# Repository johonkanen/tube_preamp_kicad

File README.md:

# tube_preamp_kicad

KiCad 10 migration of the 3-tube 12AX7 preamp (`etunen`) of the tube amplifier, from Proteus. The schematic is redrawn from
the Proteus PDF and the PCB is rebuilt from the Gerber X2 export, so that every pad, track,
via and pour carries a net from the new schematic. The IPC-D-356A netlist of the CADCAM export
is the reference that every check compares against.

This is **rev A, the as-built baseline**. The redesign (ribbon cables, PCB-mount pots, the new
power section) starts from it. The amplifier project, its specification and the hardware state
are in [tube_amplifier_kicad](https://github.com/johonkanen/tube_amplifier_kicad), which includes
this repo as a submodule once the conversion is verified.

## Method

The shared [proteus2kicad](https://github.com/johonkanen/proteus2kicad) tools, a submodule in
`tools/p2k` (clone with `git clone --recurse-submodules`, or run `git submodule update --init`).
The phases and checks are in `tools/p2k/CONVERSION_PLAYBOOK.md`. Everything specific to this
board is in `p2k_config.py`.

## Status

Conversion plan: [PLAN.md](PLAN.md); progress: [STATUS.md](STATUS.md); prompt for the next agent session: [next_prompt.md](next_prompt.md).

Phase 0 (skeleton and inventory) done 2026-11-20: `p2k_config.py` complete, `reference/`
tables from the IPC netlist. Phase 1 (schematic) done 2026-11-20: `lib/part_map.csv` (163 parts),
`lib/tube_preamp.kicad_sym` (9 symbols, pins = IPC ids), 5 sheets drawn by `tools/sheets/sheet01-05.py`:
163/163 parts, the KiCad netlist equals the Proteus IPC netlist (98 nets, 0 wrong-net pins), ERC
0 errors / 0 warnings. Phase 2 (footprints) done 2026-11-20: `tools/gen_footprints.py` →
`lib/footprint_map.csv` and `lib/tube_preamp.pretty`, all 163 parts fit the IPC pads (worst residual
0.001 mm), pin order checked (`tools/check_pin_order.py`). User decisions 2026-11-20: the noval
sockets are on the solder side (bottom footprint in Phase 5), the KiCad drills are kept (`DRILL_SMALLER`).
Phase 3 (PCB) done 2026-11-20: `tools/make_pcb.sh` builds `kicad/tube_preamp.kicad_pcb`
reproducibly (747 tracks, 14 vias, 13 mounting holes H101-H113), copper 0 shorts / 0 orphans / 0
opens, `check_board` OK, DRC 0 shorts / 0 unconnected / 0 parity / no unaccepted errors (user
decision 2026-11-20: round 1.5 mm TO-92 pad 1 on Q1-Q9). Still open for the user: the values of R13,
R22, R27, R30, R34, R51 and Q4. Phase 4 (independent verification, a fresh session) done 2026-11-20: `p2k ipc356_diff` (KiCad's own
IPC-D-356 export vs the Proteus file: 366/366 records within 0.05 mm, 98 nets 1:1) and the gerber
round trip `tools/roundtrip.py` (copper XOR per layer: only pad-shape differences; drills 366/366;
the 2010 Excellon 364/364 plus the 2 vias added in October 2010) pass and are in `tools/check_all.sh`;
the PDF was re-read against the IPC on all five sheets without a disagreement.
Phase 5 (clean-up) done 2026-11-20: the noval sockets U1-U3 are on the bottom side with the standard
noval numbering (footprint built mirrored; copper, pads and nets unchanged), references placed by
`place_refdes`, the short Proteus track pieces kept as drawn (user decisions), and two hardened checks
from the PI / FX loop board (`tools/check_drill_smaller.py`, joined no-connect pins in `tools/compare.py`
/ `tools/erc.sh`). `tools/check_all.sh`: ALL CHECKS PASSED. **The conversion is complete.** The board
is still generated by `tools/make_pcb.sh` (STATUS.md "Phase 5").
Design fixes 2026-11-20 (user decisions, STATUS.md "Design fixes 2026-11-20"): the G5V-2 relay symbol
carries Omron's terminal names (finding 14; pin numbers = Proteus ids, no copper change), the 9
dangling / zero-length Proteus track pieces of findings 16 / 20 are not built (`REMOVED_TRACKS`, pinned by
`tools/check_removed_tracks.py`; 738 tracks), the component values stay as they are (the board will be
redesigned) and finding 4 is unchanged. `tools/check_all.sh`: ALL CHECKS PASSED. Next: the shared-tool
migration, then the board stops being generated (next_prompt.md).
Shared-tool migration 2026-11-20 (STATUS.md "Shared-tool migration 2026-11-20"), done: p2k a9a286c;
the board-local tools named above (`compare.py`, `erc.sh`, `check_pin_order.py`, `rename_holes.py`,
`roundtrip.py`, `check_drill_smaller.py`, `excellon_metric.py`, `measure_gaps.py`) are replaced by the
shared tools and `p2k_config.py` keys (`tools/make_pcb.sh` = `p2k make_pcb`); no strict-check opt-outs;
kept: `tools/check_removed_tracks.py`. Design change (electrically identical, same copper): the relays
RLY1-RLY5 carry the Omron pin numbers (`IPC_PIN_IDS`) with KiCad's stock G5V-2 symbol and footprint.
Generation stopped 2026-11-20 (user decision, STATUS.md "Generation stopped 2026-11-20"): the
committed KiCad files are the source from now on; the generators named above are frozen in `tools/generate/`.

Built in about 2010 from the June 2010 Gerbers (`source/fab_2010/`). The Proteus layout was edited in October 2010: Q6 pin 3 moves from net J1 to a new net J4 (Q6-3, Q9-3, pad D), plus a ground reroute. The export in `source/cadcam/` is the October version. Holes, outline and tube sockets are identical to the fabricated board. Accepted as the baseline, since the board gets redesigned.

## Working on rev A (since 2026-11-20)

Rev A is no longer generated from the Proteus data. The committed KiCad files are the source:
open `kicad/tube_preamp.kicad_pro` in KiCad 10 and edit the schematic, the board and `lib/`
there. Then run `tools/check_all.sh` (must end with ALL CHECKS PASSED). It checks the
committed files against the Proteus truth (IPC netlist, gerbers, drills) and KiCad's rules:
netlist, ERC, footprints, pin order, board pads / vias / holes, copper connectivity, DRC with
parity, KiCad's IPC-D-356 export and the gerber round trip. A change that makes the board
differ from Proteus fails a check on purpose: record it as a deviation (the matching
`p2k_config.py` key with a reason and a line in STATUS.md), never hide it.

The generator scripts in `tools/generate/` are frozen history (how every file was made) and
must not be run; `tools/generate/make_pcb.sh` refuses without `--force-regenerate`.

**Rev B** (the redesign, preamp design D) is a separate KiCad project in [`rev_b/`](rev_b/),
worked on in its own sessions; `tools/check_all.sh` checks only rev A.

## Source

etunen.DSN/.LYT (Proteus 7, 2010), opened and saved in Proteus 8.12 as `etunen.pdsprj`. Exported 2026-11-19 from Proteus 8.12 SP2: schematic PDF, Gerber X2 CADCAM (metric)
with the IPC-D-356A netlist.

## Mechanical baseline

From the export (the fit reference for the redesign; the KiCad file is
`mechanical/preamp_etunen.kicad_pcb` in tube_amplifier_kicad):

```
outline: 382.79 x 71.91 mm, lower-left corner at (-195.357, -45.730) in the Proteus frame
copper layers: 2; components: 163; mounting holes: 13
mounting holes (relative to the lower-left outline corner, mm; KiCad refdes H101-H113,
mapping in STATUS.md "Phase 3"):
  H1: x   55.992  y   58.550  drill 3.00 plated
  H2: x  163.492  y   61.550  drill 3.00 plated
  H3: x  194.492  y   58.550  drill 3.00 plated
  H4: x  174.492  y   36.050  drill 3.00 plated
  H5: x   34.992  y   36.050  drill 3.00 plated
  H6: x    5.492  y    5.050  drill 3.00 plated
  H7: x    5.492  y   66.050  drill 3.00 plated
  H8: x  247.492  y   61.550  drill 3.00 plated
  H9: x  277.492  y   58.550  drill 3.00 plated
  H10: x  258.492  y   36.050  drill 3.00 plated
  H11: x  378.492  y    5.050  drill 3.00 plated
  H12: x  378.492  y   66.050  drill 3.00 plated
  H13: x   24.492  y   61.550  drill 3.00 plated
```

## Layout

```
source/         Proteus exports (read-only)
  cadcam/         Gerber X2 export with the IPC-D-356A netlist (the reference)
  schematic_pdf/  schematic PDF to redraw from
  *.pdsprj        Proteus project (schematic values, devices, packages, pin names)
  fab_2010/       the RS-274X Gerbers the boards were made from (June 2010)
reference/      tables derived from the IPC netlist (p2k ipc356): pads, pin -> net, pins by net
tools/p2k/       proteus2kicad (submodule)
kicad/, lib/     rev A KiCad project and libraries (the source since 2026-11-20)
tools/check_all.sh  every verification step (run at the start and end of a session)
tools/check_removed_tracks.py  board check: the decided removed Proteus track pieces
tools/generate/  frozen generators (history, do not run)
rev_b/          rev B, the redesign (separate project)
p2k_config.py   board configuration for the tools
```

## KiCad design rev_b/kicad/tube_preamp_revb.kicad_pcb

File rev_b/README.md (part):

# Preamp rev B (design D): first-draft schematic

The next preamp board, from the simulations in
[tube_amplifier_kicad](https://github.com/johonkanen/tube_amplifier_kicad) (branch `tube_preamps`):
`sim/preamp_voicing` (design D, `ours/chain_d.py` + `ours/fit_design_D.json`) and
`docs/preamp_board_plan.md`. Rev A (the as-built `etunen` conversion) at the repo root is not
touched; `rev_b/` is its own p2k board root (`p2k_config.py`, PROJECT `tube_preamp_revb`).

Three channels (clean / crunch / lead) on one shared 3x12AX7 cascade: S1, S2, (S5), S3, a
self-biased CF, three Baxandalls, S4 recovery, attenuator, output mute. Switching follows CH-5
(DC-neutral): 7 MMBFJ113 shunts (6 pot-set selections + output mute), 5 2N7002 low-side AC
cathode networks, 4 G6K-2 relays (S2 treble bleed, S5 routing, c2, S3 treble bleed), 16 control
lines from an MCP23S17.

## Build

```
python3 rev_b/tools/make_lib.py          # lib/tube_preamp_revb.kicad_sym from KiCad's stock libraries (flattened)
python3 rev_b/tools/make_project.py      # project, root sheet, empty sub-sheets
python3 -I rev_b/tools/make_footprints.py  # project footprints, lib/footprint_map.csv (from make_bom.py), fp-lib-table
python3 rev_b/tools/sheets/draw_all.py   # draws all five sheets (overwrites them); Footprint fields from the map
python3 -I rev_b/tools/make_footprints.py --check   # every part has a footprint, symbol pins = pads
tools/p2k/bin/kipy rev_b/tools/make_pcb.py   # NEW board from the netlist (refuses once it has tracks)
```

`make_pcb.py` is for the start only: once placement begins, the board is edited in KiCad and
schematic changes go in with Update PCB from Schematic (the footprints carry the schematic links).

The sheets are generated: edit `tools/sheets/draw_all.py`, not the `.kicad_sch` files, until the
draft is frozen. Drawing style is netlist-first (parts on a grid, a wire stub and a label on every
pin), exact for ERC and the netlist; a tidy layout pass comes later. ERC: 0 errors, 0 warnings
(KiCad 10, `kicad-cli sch erc`).

| Sheet | Contents |
|---|---|
| 01 | Input jack, 68k, S1 (V1 pins 1-3) with its DC 2.7k and two MOSFET AC networks; per-channel coupling cap, gain pot (ribbon), bright cap, JFET T-selection into S2 |
| 02 | S2 (V1 6-8), S5 (V2 1-3), S3 (V2 6-8); relays K201-K204; the AC networks |
| 03 | CF (V3 1-3, grid at 90 V), three Baxandalls (pots on the ribbons), JFET-selected post-gain into S4 (V3 6-8), 330k / 220k attenuator, output mute JFET |
| 04 | Control ribbon, MCP23S17, 2x DG412 (JFET gates 0 / -15 V), 74LVC1G08 (unmute = GPA6 AND MUTE_ALL_N), ULN2003 (relay coils) |
| 05 | B+ regulator (as `sim/preamp_supply/reg.py`), RC decoupling per stage, 90 V CF bias, heaters + reference jumper, three 26-pin pot ribbons, output |

## Draft decisions and open items

- Values follow the 2026-11-20 refit of design D (gain-knob penalty): the lead's 470k pad and 1 nF
  bright cap are gone. The refit also gave S2 a lead-only 4.7k + 22 µF network; it is drawn
  **permanent** (no switch), in parallel with the clean / crunch switched 22 µF, which keeps the
  control lines at 16. Simulated: identical fit (crunch cost 10.03 → 10.04, others unchanged).
- Fail-safe muting: DG412 is normally open, so with no logic supply, reset, or no -15 V every JFET
  gate sits at 0 V (JFET on) and the output is muted; a missing control ribbon pulls MUTE_ALL_N low.
- 2N7002 gates run from the expander's 5 V (the plan said 10 V); Rds(on) at 5 V is a few ohms
  against 1.5k-10k cathode resistors. Check the 22 µF / 1M bleed timing with the real Vgs(th).
- Relays: Omron G6K-2F-Y 5 VDC, decided 2026-11-22 (main session; same part on the PI + FX board).
  Checked against the Omron G6K datasheet (top view): coil + pin 1, - pin 8; pole 1 COM 3, NC 4,
  NO 2; pole 2 COM 6, NC 5, NO 7. Every switched function is on the NO contacts, so energized =
  the lead / crunch setting and an unpowered board sits in the clean wiring (the first draft had
  2 / 4 and 5 / 7 the other way round; fixed 2026-11-22). Coil 21.1 mA at 5 V (237 Ω), 4 coils.
  Contacts carry no DC (10M bleeds, CH-5 rule 3); K201 / K204 sit at the B+ DC level, within the
  coil-to-contact insulation of the -Y (3.2 mm) version.
- Open from the fit: the crunch's gain knob stays at 0.9 and its JFET node at 9.3 V peak with 1 V
  in (limit 8 V); a pad on the crunch's input network is the next fix. The footprint is in: R119
  (0805) between C108 and the crunch gain pot's top, fitted as a 0R link until the voicing sim
  sets the value (2026-11-22).
- B+ decoupling resistors (3.3k / 6.8k / 10k / 10k) are provisional until the stage currents are
  summed; the simulations used 300 V at the plates' supply. All four are 2512 (2026-11-22), so a
  later value change doesn't touch the layout.
- HV resistors split for 200 V 2512 parts (2026-11-21): the B+ bleed is R508 + R518 (2 x 220k, 165 V
  each) and the VB90 divider top R513 + R519 (2 x 330k, 115 V each; 660k with R514 270k gives
  VB90 = 0.29 x BP4, about +2 % on the old 680k). The regulator's foldback resistor is R507 + R520 +
  R521 (3 x 270k = 810k, was one 820k 1206): it sees the whole 430 V raw rail at start-up or into a
  short, 145 V per part. The reference filter Rf is R502 + R525 + R526 (3 x 330k = 990k, was one
  1M 1206; 2026-11-22, found by the PI + FX session): the 390 V zener reference sits across it while
  C501 charges, 130 V per part. Checked the rest of the board from the netlist: no other resistor
  sees more than 200 V in normal operation. The 10M cap bleeds (relay networks) see under 100 V at
  start-up and short recovery, and only a ~300 V pulse (22-220 ms) if B+ is hard-shorted; kept as 1206 (main session
  2026-11-22: the 200 V rule covers normal operation and start-up, a decaying fault pulse within the
  part's short-time overload rating is acceptable).
- Regulator short-circuit protection by thermal foldback (user 2026-11-21): Q502 is an STD4N80K5 DPAK
  on a copper pour, and Q503 (the current-limit NPN) sits on the same pour, thermally coupled but
  not electrically connected. Q503's Vbe falls about 2 mV/K, so a short heats the pour and folds the
  current back further; R507 stays about 820k (now 3 x 270k), R504 goes 20R -> 13R to keep the normal limit above the
  10-15 mA load when Q503 is warm. Simulated (sim/preamp_supply model, whole circuit at one
  temperature, 330 V output):

  | Q503 temperature | 0 C | 27 C | 50 C | 70 C | 85 C | 100 C |
  |---|---|---|---|---|---|---|
  | Normal limit (mA) | 38 | 33 | 28.5 | 25 | 22 | 19 |
  | Into a short (mA / W in Q502) | 16.5 / 7.1 | 12.3 / 5.3 | 8.6 / 3.7 | 5.4 / 2.3 | 3.0 / 1.3 | 0.5 / 0.2 |

  Start-up and recovery after a short work at every temperature. With about 30 K/W from the pour
  to Q503 the short settles near 80 C and 2 W. Lowering R507 instead was rejected: 700k gives 4 mA
  at 27 C but no start-up above about 70 C. Bench check: short B+ and watch the current settle.
- Drain resistor R522 + R523 + R524 (3 x 1.5k 2512 = 4.5k, raw rail to Q502's drain, placed off
  Q502's pour), user 2026-11-22 with the 70 C design temperature under the plate: it takes about
  68 V of the drop, so Q502 dissipates 0.5 W instead of 1.5 W and Q503 stays near 87-91 C at 70 C
  ambient (limit about 22 mA, 19 mA at 420 V raw; start-up works). Without it the regulator lost
  start-up above 60 C ambient. Short unchanged. See tube_amplifier_kicad docs/preamp_regulator.md
  and sim/preamp_supply/results/thermal_foldback.md. Raw rail at 480 V (HV supplies' trip level,
  2026-11-22): every raw-rail part is within its rating (LND150 sees about 90 V, R3 160 V per part);
  the regulator keeps running, but held at 480 V with Q503 at 85 C or more it doesn't start or
  recover from a short. Fine as a transient, sustained raw at most 450 V (preamp_regulator.md).
- Footprints (2026-11-22): every part has one, chosen on its line in `tools/make_bom.py` (the BOM
  and the footprints come from the same list; [bom/](bom/README.md), JLC search and stock check from
  the jlc-tools submodule rev_b/tools/jlc). KiCad stock footprints except three Faston tab
  footprints and the rev A noval socket (rev_b/lib/tube_preamp_revb.pretty). The generic transistor
  symbols got package pin numbers (make_lib.py: Q501 / Q502 1 G, 2 D, 3 S; Q503 1 B, 2 E, 3 C).
  Values set at the same time: R327 300k (for the PI + FX's 1 MΩ input), C105 / C108 / C111
  marked 630 V.
- Grounding (tube_amplifier_kicad docs/grounding.md §5a, confirmed by the user 2026-11-21): AGND
  (GNDA) is the signal and power star, its only entry J501 pin 2; the switch references (JFET and
  MOSFET sources, their gate caps, the JFET-gate pull-downs R419-R425) are AGND. Sheet 04's logic,
  expander pull-downs, ULN2003, relay coils and DG412 GND / rail decoupling are a DGND (GNDD) island
  joined to AGND only by R426 10 Ω ∥ C407 100 nF next to J401. Chassis bond: the CHASSIS pad J102
  next to J101: insulated input jack plus a bolted chassis tag wired to J102 (user, 2026-11-21;
  interfaces.md IF-1). J507 pin 3 is the shield, soft-tied here (R517 10 Ω ∥ C509 100 nF), solid at the
  PI + FX end. Heater reference stays on J503.
- Layout constraint (tube_amplifier_kicad docs/interfaces.md §12.2, components down confirmed by the
  user 2026-11-21; replaces the earlier "headers pass under the front edge" rule): the board hangs
  15 mm below the plate with its components down and the novals on the solder side. Along the front
  edge, at least at the three pot-ribbon positions, keep a strip 15 mm deep where no part is taller
  than 5 mm (SMD passives and SOT-23 only: no film or electrolytic caps, relays or headers). J504-J506
  are vertical shrouded headers on the downward face, set back about 20 mm from the front edge, and
  nothing (mated socket included) protrudes past the edge. Final check: the 3D fit with the front
  panel board once this board is laid out. Standoffs 15 mm; the `etunen` outline stays.
- Pot direction: on every pot ribbon line the CW (clockwise-end) lug takes the TOP net. Bass and
  treble: TOP is the boost end (C1 / C3 from the CF), BOT the cut end (22k to GND), so clockwise =
  more; gain and post: TOP is the signal, the bottom GND (confirmed to the front panel session
  2026-11-21). Pots (front panel board, decided 2026-11-22): Alpha 16 mm PCB pots (RV16AF-41
  class, M7 bushing); gain and post-gain 1M log, treble and bass 1M linear.
- Start-up (2026-11-22): the amp plays before Linux boots; the control board's FPGA brings it up on
  its own, so this board sees RESET_N, the SPI write, then unmute a few seconds after power-on.
- J401 placement: the control board (126 x 92 mm at chassis x 426-552, y 30-122) has its preamp
  ribbon connector on its front edge at about x 438-464, roughly 50-80 mm from J401 at this
  board's right end (main session 2026-11-22).
- Output (J507), agreed in tube_amplifier_kicad docs/interfaces.md §10 (2026-11-20): Zout about
  140k; the PI + FX input is ≥ 1 MΩ with a buffer at its connector, total capacitance on OUT
  ≤ 50 pF. The 1 MΩ load costs about 1.1 dB: the attenuator's 330k is now 300k (R327, 2026-11-22). Fallback if the cable can't be short: the divider moves to the receiver, which needs
  a re-run of sim/preamp_voicing/switching_real.py (mute depth). The connector pinouts are the
  interfaces.md contract: propose changes through the main-branch session.

## Layout (decisions 2026-11-22, user: "make decisions that allow completing the layout")

`kicad/tube_preamp_revb.kicad_pcb` is started (`tools/make_pcb.py`): outline, holes, sockets, the
interface connectors placed, net classes and clearance rules set, every other part parked below
the board by sheet. DRC with schematic parity: only the unrouted connections. Choices made so the
layout can be finished; to check against the other boards when they are laid out.

- **Frame:** the `etunen` outline (382.79 x 71.91 mm) in rev A's coordinates: chassis x = board
  x + 198.73, chassis y = board y + 42.35. The top edge (y -26.175) is the front, the left end is
  the input end. KiCad's front (F) side is the component side, facing down.
- **Board:** 2 layers, 1.6 mm, 2 oz copper (the regulator's 40 K/W pour estimate assumed 2 oz; set it in
  Board Setup > Physical Stackup before the fab outputs, the generated board has the default 1 oz).
  Min track / space 0.2 mm.
- **Sockets:** V1-V3 on the solder side (B), at rev A's U1-U3 positions and orientation (pads
  checked: 0.00 mm). The rev A footprint got a round courtyard and silk outline (the rectangle
  clipped the standoff holes H103-H105).
- **Mounting holes:** H101-H113 at the rev A positions, 3.2 mm, not plated, with an 8 mm copper
  keep-out. The chassis bond is J102 only (grounding.md §5a), so no hole is plated.
- **Pot ribbons:** J504 (clean) and J505 (crunch) between V1 and V2, J506 (lead) between V2 and
  V3, long axis along the front edge, body front edge 20 mm behind the board edge, odd (GND) pins
  on the rear row. Centres at board x -112 / -62 / 25 = **chassis x 86.7 / 136.7 / 223.7**, body
  front edge at chassis y 36.2. Three 41 mm headers don't fit in one gap between sockets; the
  lead's gain-pot lines then run about 120 mm to V1, inside the ground pour. Each channel's
  Baxandall and post-gain JFET go next to its header.
- **Other connectors:** J101 input and J102 chassis tab at the left end (chassis x about 9);
  J401 at the right end, clear of H102 (chassis x 375-385, y 27-54, about 60 mm from the control
  board's connector); J501 B+ raw tabs at the rear right (chassis x 357 / 372); J502 heater tabs
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
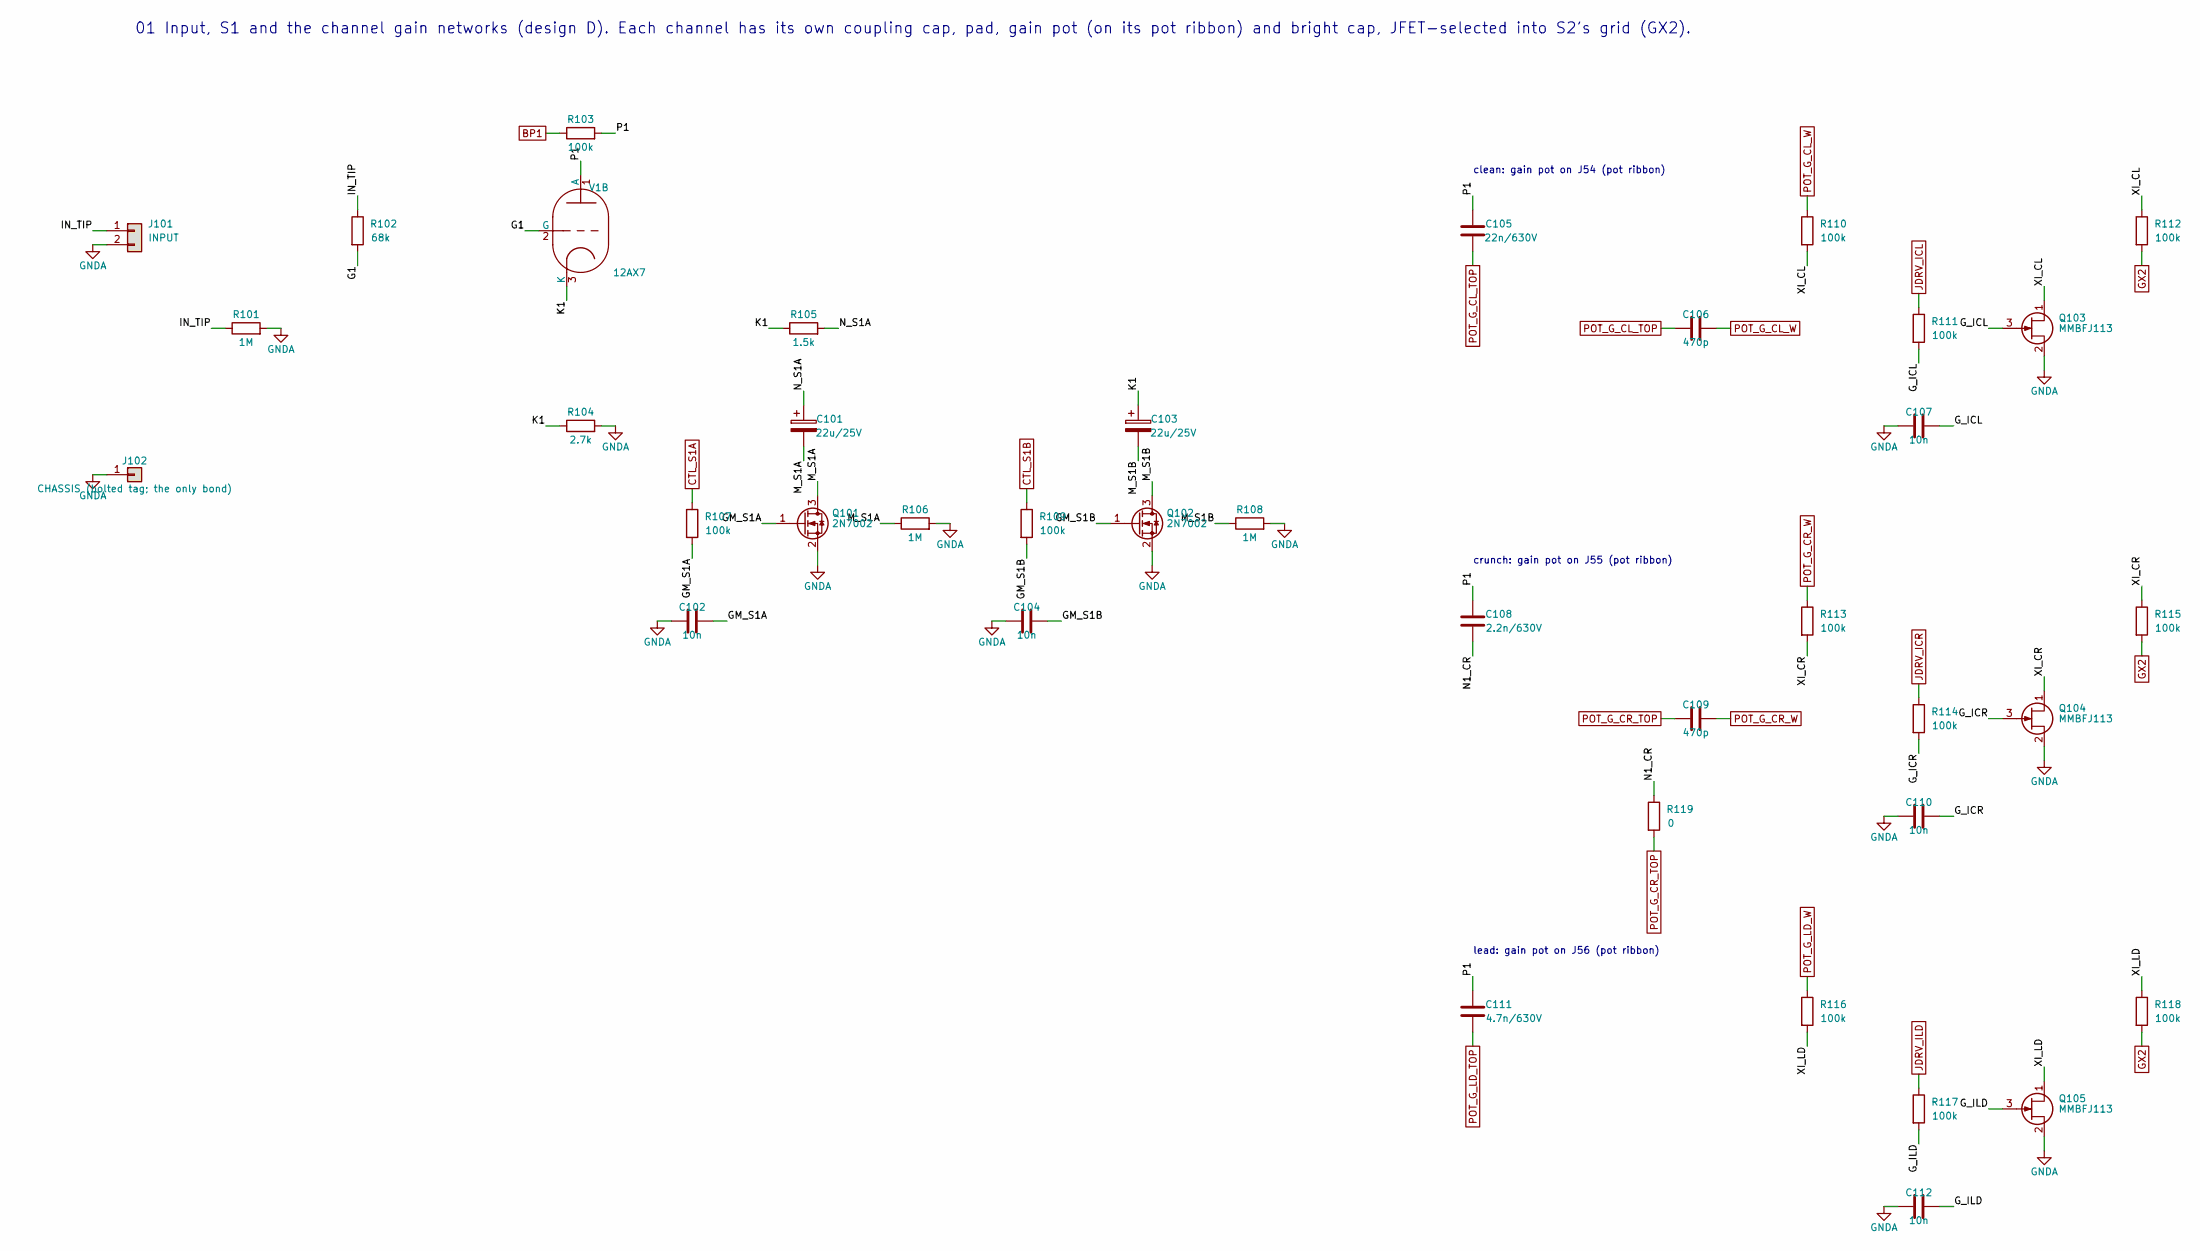
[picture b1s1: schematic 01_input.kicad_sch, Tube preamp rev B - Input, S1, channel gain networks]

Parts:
C101, C103: 22u/25V; CP_Elec_5x5.4
C102, C104, C107, C110, C112: 10n; C_0603_1608Metric
C105: 22n/630V; C_Rect_L10.0mm_W4.0mm_P7.50mm_MKS4
C106, C109: 470p; C_0805_2012Metric
C108: 2.2n/630V; C_1206_3216Metric
C111: 4.7n/630V; C_1206_3216Metric
J101: INPUT; Molex_KK-254_AE-6410-02A_1x02_P2.54mm_Vertical
J102: CHASSIS (bolted tag; the only bond); Faston_Tab_6.3mm_x1
Q101, Q102: 2N7002; SOT-23
Q103, Q104, Q105: MMBFJ113; SOT-23
R101, R106, R108: 1M; R_0805_2012Metric
R102: 68k; R_0805_2012Metric
R103: 100k; R_2512_6332Metric
R104: 2.7k; R_0805_2012Metric
R105: 1.5k; R_0805_2012Metric
R107, R109, R111, R114, R117: 100k; R_0603_1608Metric
R110, R112, R113, R115, R116, R118: 100k; R_0805_2012Metric
R119: 0; R_0805_2012Metric
V1: 12AX7; Valve_Noval_Belton_PCD21.00mm

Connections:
/01 Input, S1, channel gain networks/G1: R102.2, V1.2 (G)
/01 Input, S1, channel gain networks/GM_S1A: C102.1, Q101.1 (G), R107.2
/01 Input, S1, channel gain networks/GM_S1B: C104.1, Q102.1 (G), R109.2
/01 Input, S1, channel gain networks/G_ICL: C107.1, Q103.3 (G), R111.2
/01 Input, S1, channel gain networks/G_ICR: C110.1, Q104.3 (G), R114.2
/01 Input, S1, channel gain networks/G_ILD: C112.1, Q105.3 (G), R117.2
/01 Input, S1, channel gain networks/IN_TIP: J101.1, R101.1, R102.1
/01 Input, S1, channel gain networks/K1: C103.1, R104.1, R105.1, V1.3 (K)
/01 Input, S1, channel gain networks/M_S1A: C101.2, Q101.3 (D), R106.1
/01 Input, S1, channel gain networks/M_S1B: C103.2, Q102.3 (D), R108.1
/01 Input, S1, channel gain networks/N1_CR: C108.2, R119.1
/01 Input, S1, channel gain networks/N_S1A: C101.1, R105.2
/01 Input, S1, channel gain networks/P1: C105.1, C108.1, C111.1, R103.2, V1.1 (A)
/01 Input, S1, channel gain networks/XI_CL: Q103.1 (D), R110.2, R112.1
/01 Input, S1, channel gain networks/XI_CR: Q104.1 (D), R113.2, R115.1
/01 Input, S1, channel gain networks/XI_LD: Q105.1 (D), R116.2, R118.1
BP1: R103.1; also elsewhere on the board
CTL_S1A: R107.1; also elsewhere on the board
CTL_S1B: R109.1; also elsewhere on the board
GNDA: C102.2, C104.2, C107.2, C110.2, C112.2, J101.2, J102.1, Q101.2 (S), Q102.2 (S), Q103.2 (S), Q104.2 (S), Q105.2 (S), R101.2, R104.2, R106.2, R108.2; also elsewhere on the board
GX2: R112.2, R115.2, R118.2; also elsewhere on the board
JDRV_ICL: R111.1; also elsewhere on the board
JDRV_ICR: R114.1; also elsewhere on the board
JDRV_ILD: R117.1; also elsewhere on the board
POT_G_CL_TOP: C105.2, C106.1; also elsewhere on the board
POT_G_CL_W: C106.2, R110.1; also elsewhere on the board
POT_G_CR_TOP: C109.1, R119.2; also elsewhere on the board
POT_G_CR_W: C109.2, R113.1; also elsewhere on the board
POT_G_LD_TOP: C111.2; also elsewhere on the board
POT_G_LD_W: R116.1; also elsewhere on the board

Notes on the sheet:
01 Input, S1 and the channel gain networks (design D). Each channel has its own coupling cap, pad, gain pot (on its pot ribbon) and bright cap, JFET-selected into S2's grid (GX2).
clean: gain pot on J54 (pot ribbon)
crunch: gain pot on J55 (pot ribbon)
lead: gain pot on J56 (pot ribbon)

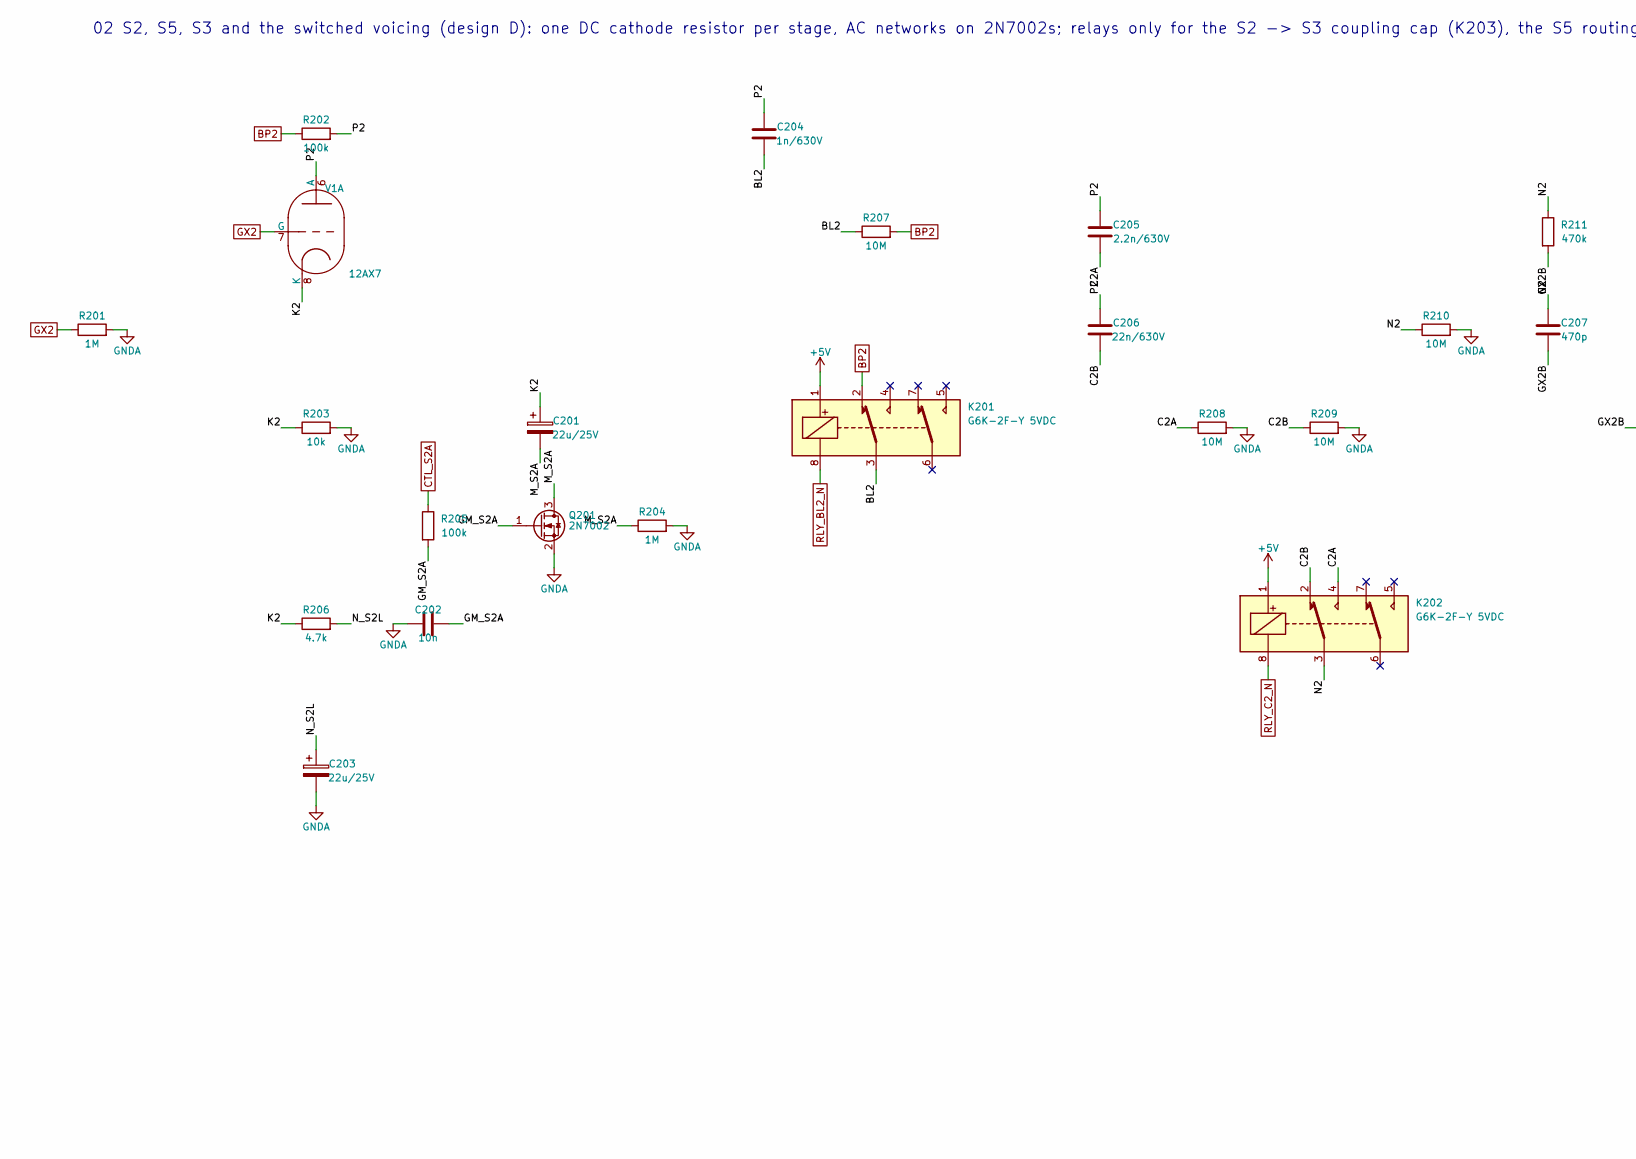
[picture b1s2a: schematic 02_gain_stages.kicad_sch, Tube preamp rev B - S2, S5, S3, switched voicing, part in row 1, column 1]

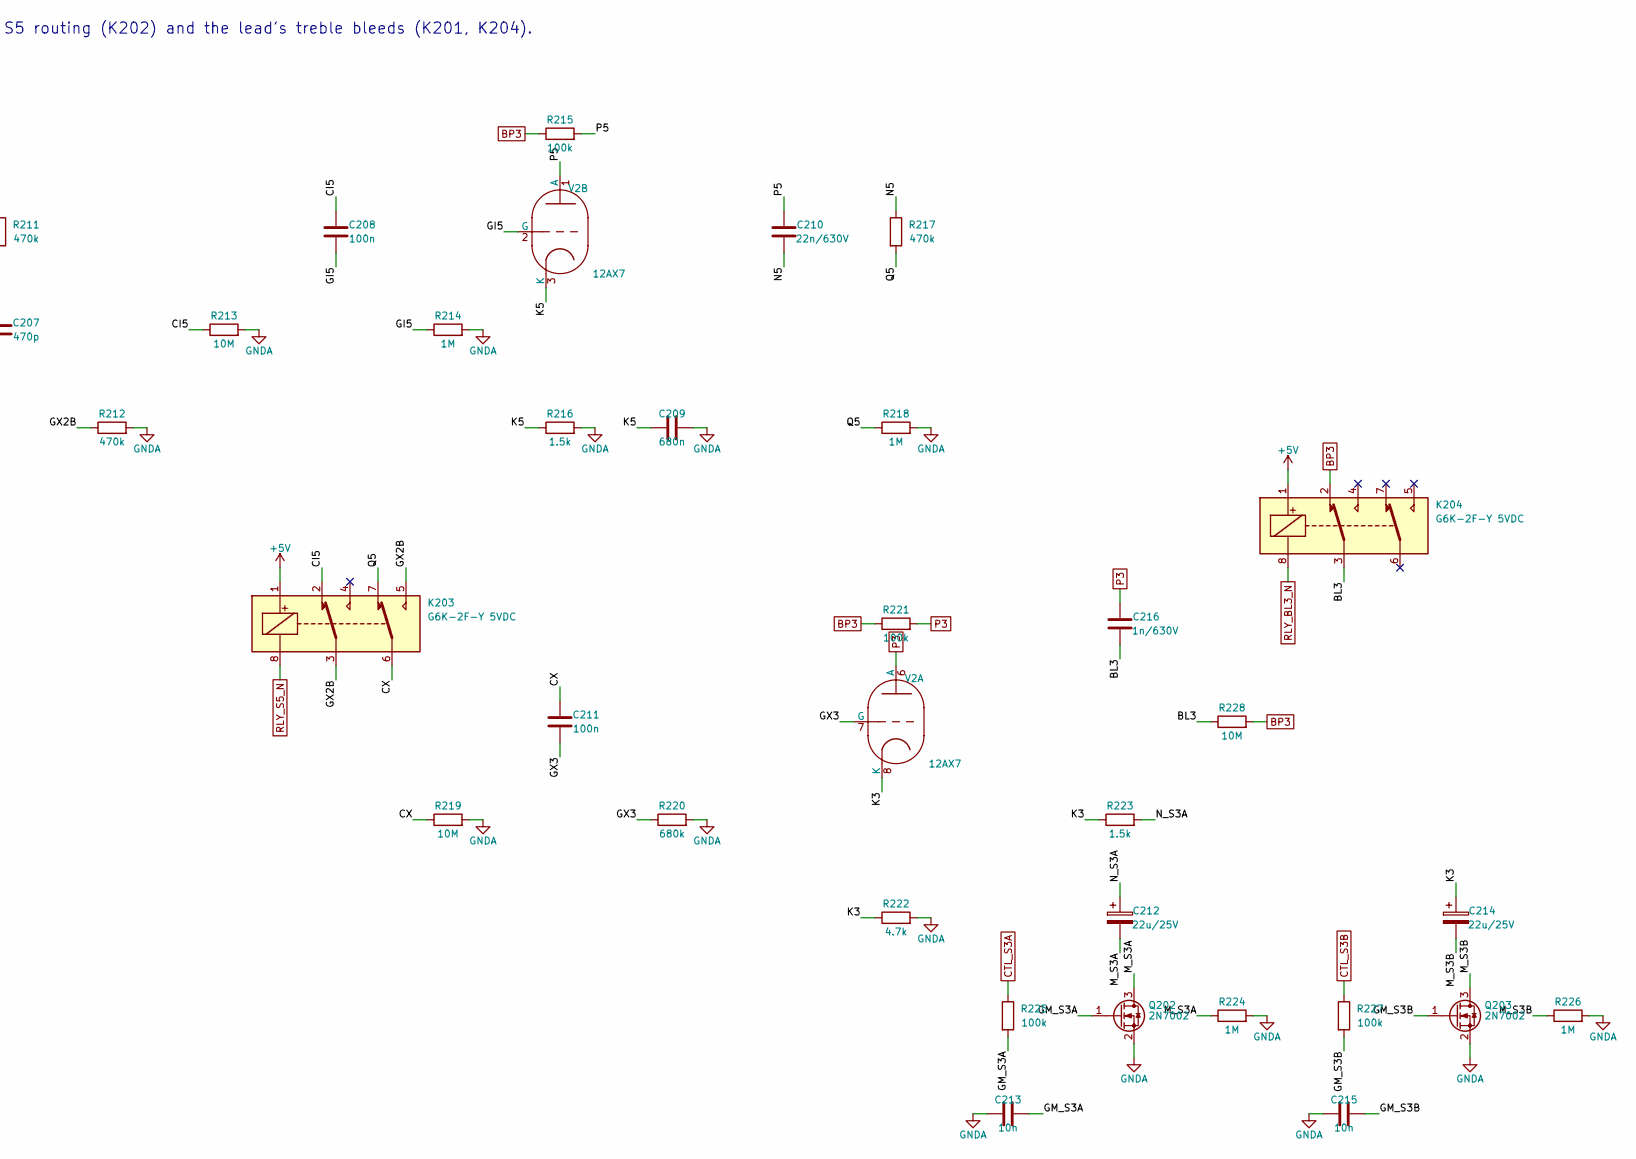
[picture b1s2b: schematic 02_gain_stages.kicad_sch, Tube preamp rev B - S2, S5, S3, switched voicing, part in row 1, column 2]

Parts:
C201, C203, C212, C214: 22u/25V; CP_Elec_5x5.4
C202, C213, C215: 10n; C_0603_1608Metric
C204, C216: 1n/630V; C_1206_3216Metric
C205: 2.2n/630V; C_1206_3216Metric
C206, C210: 22n/630V; C_Rect_L10.0mm_W4.0mm_P7.50mm_MKS4
C207: 470p; C_0805_2012Metric
C208, C211: 100n; C_1206_3216Metric
C209: 680n; C_1206_3216Metric
K201, K202, K203, K204: G6K-2F-Y 5VDC; Relay_DPDT_Omron_G6K-2F-Y
Q201, Q202, Q203: 2N7002; SOT-23
R201, R204, R214, R218, R224, R226: 1M; R_0805_2012Metric
R202, R215, R221: 100k; R_2512_6332Metric
R203: 10k; R_0805_2012Metric
R205, R225, R227: 100k; R_0603_1608Metric
R206, R222: 4.7k; R_0805_2012Metric
R207, R208, R209, R210, R213, R219, R228: 10M; R_1206_3216Metric
R211, R212, R217: 470k; R_0805_2012Metric
R216, R223: 1.5k; R_0805_2012Metric
R220: 680k; R_0805_2012Metric
V1, V2: 12AX7; Valve_Noval_Belton_PCD21.00mm

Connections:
+5V: K201.1, K202.1, K203.1, K204.1; also elsewhere on the board
/02 S2, S5, S3, switched voicing/BL2: C204.2, K201.3, R207.1
/02 S2, S5, S3, switched voicing/BL3: C216.2, K204.3, R228.1
/02 S2, S5, S3, switched voicing/C2A: C205.2, K202.4, R208.1
/02 S2, S5, S3, switched voicing/C2B: C206.2, K202.2, R209.1
/02 S2, S5, S3, switched voicing/CI5: C208.1, K203.2, R213.1
/02 S2, S5, S3, switched voicing/CX: C211.1, K203.6, R219.1
/02 S2, S5, S3, switched voicing/GI5: C208.2, R214.1, V2.2 (G)
/02 S2, S5, S3, switched voicing/GM_S2A: C202.1, Q201.1 (G), R205.2
/02 S2, S5, S3, switched voicing/GM_S3A: C213.1, Q202.1 (G), R225.2
/02 S2, S5, S3, switched voicing/GM_S3B: C215.1, Q203.1 (G), R227.2
/02 S2, S5, S3, switched voicing/GX2B: C207.2, K203.3, K203.5, R211.2, R212.1
/02 S2, S5, S3, switched voicing/GX3: C211.2, R220.1, V2.7 (G)
/02 S2, S5, S3, switched voicing/K2: C201.1, R203.1, R206.1, V1.8 (K)
/02 S2, S5, S3, switched voicing/K3: C214.1, R222.1, R223.1, V2.8 (K)
/02 S2, S5, S3, switched voicing/K5: C209.1, R216.1, V2.3 (K)
/02 S2, S5, S3, switched voicing/M_S2A: C201.2, Q201.3 (D), R204.1
/02 S2, S5, S3, switched voicing/M_S3A: C212.2, Q202.3 (D), R224.1
/02 S2, S5, S3, switched voicing/M_S3B: C214.2, Q203.3 (D), R226.1
/02 S2, S5, S3, switched voicing/N2: C207.1, K202.3, R210.1, R211.1
/02 S2, S5, S3, switched voicing/N5: C210.2, R217.1
/02 S2, S5, S3, switched voicing/N_S2L: C203.1, R206.2
/02 S2, S5, S3, switched voicing/N_S3A: C212.1, R223.2
/02 S2, S5, S3, switched voicing/P2: C204.1, C205.1, C206.1, R202.2, V1.6 (A)
/02 S2, S5, S3, switched voicing/P5: C210.1, R215.2, V2.1 (A)
/02 S2, S5, S3, switched voicing/Q5: K203.7, R217.2, R218.1
BP2: K201.2, R202.1, R207.2; also elsewhere on the board
BP3: K204.2, R215.1, R221.1, R228.2; also elsewhere on the board
CTL_S2A: R205.1; also elsewhere on the board
CTL_S3A: R225.1; also elsewhere on the board
CTL_S3B: R227.1; also elsewhere on the board
GNDA: C202.2, C203.2, C209.2, C213.2, C215.2, Q201.2 (S), Q202.2 (S), Q203.2 (S), R201.2, R203.2, R204.2, R208.2, R209.2, R210.2, R212.2, R213.2, R214.2, R216.2, R218.2, R219.2, R220.2, R222.2, R224.2, R226.2; also elsewhere on the board
GX2: R201.1, V1.7 (G); also elsewhere on the board
P3: C216.1, R221.2, V2.6 (A); also elsewhere on the board
RLY_BL2_N: K201.8; also elsewhere on the board
RLY_BL3_N: K204.8; also elsewhere on the board
RLY_C2_N: K202.8; also elsewhere on the board
RLY_S5_N: K203.8; also elsewhere on the board

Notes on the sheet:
02 S2, S5, S3 and the switched voicing (design D): one DC cathode resistor per stage, AC networks on 2N7002s; relays only for the S2 -> S3 coupling cap (K203), the S5 routing (K202) and the lead's treble bleeds (K201, K204).

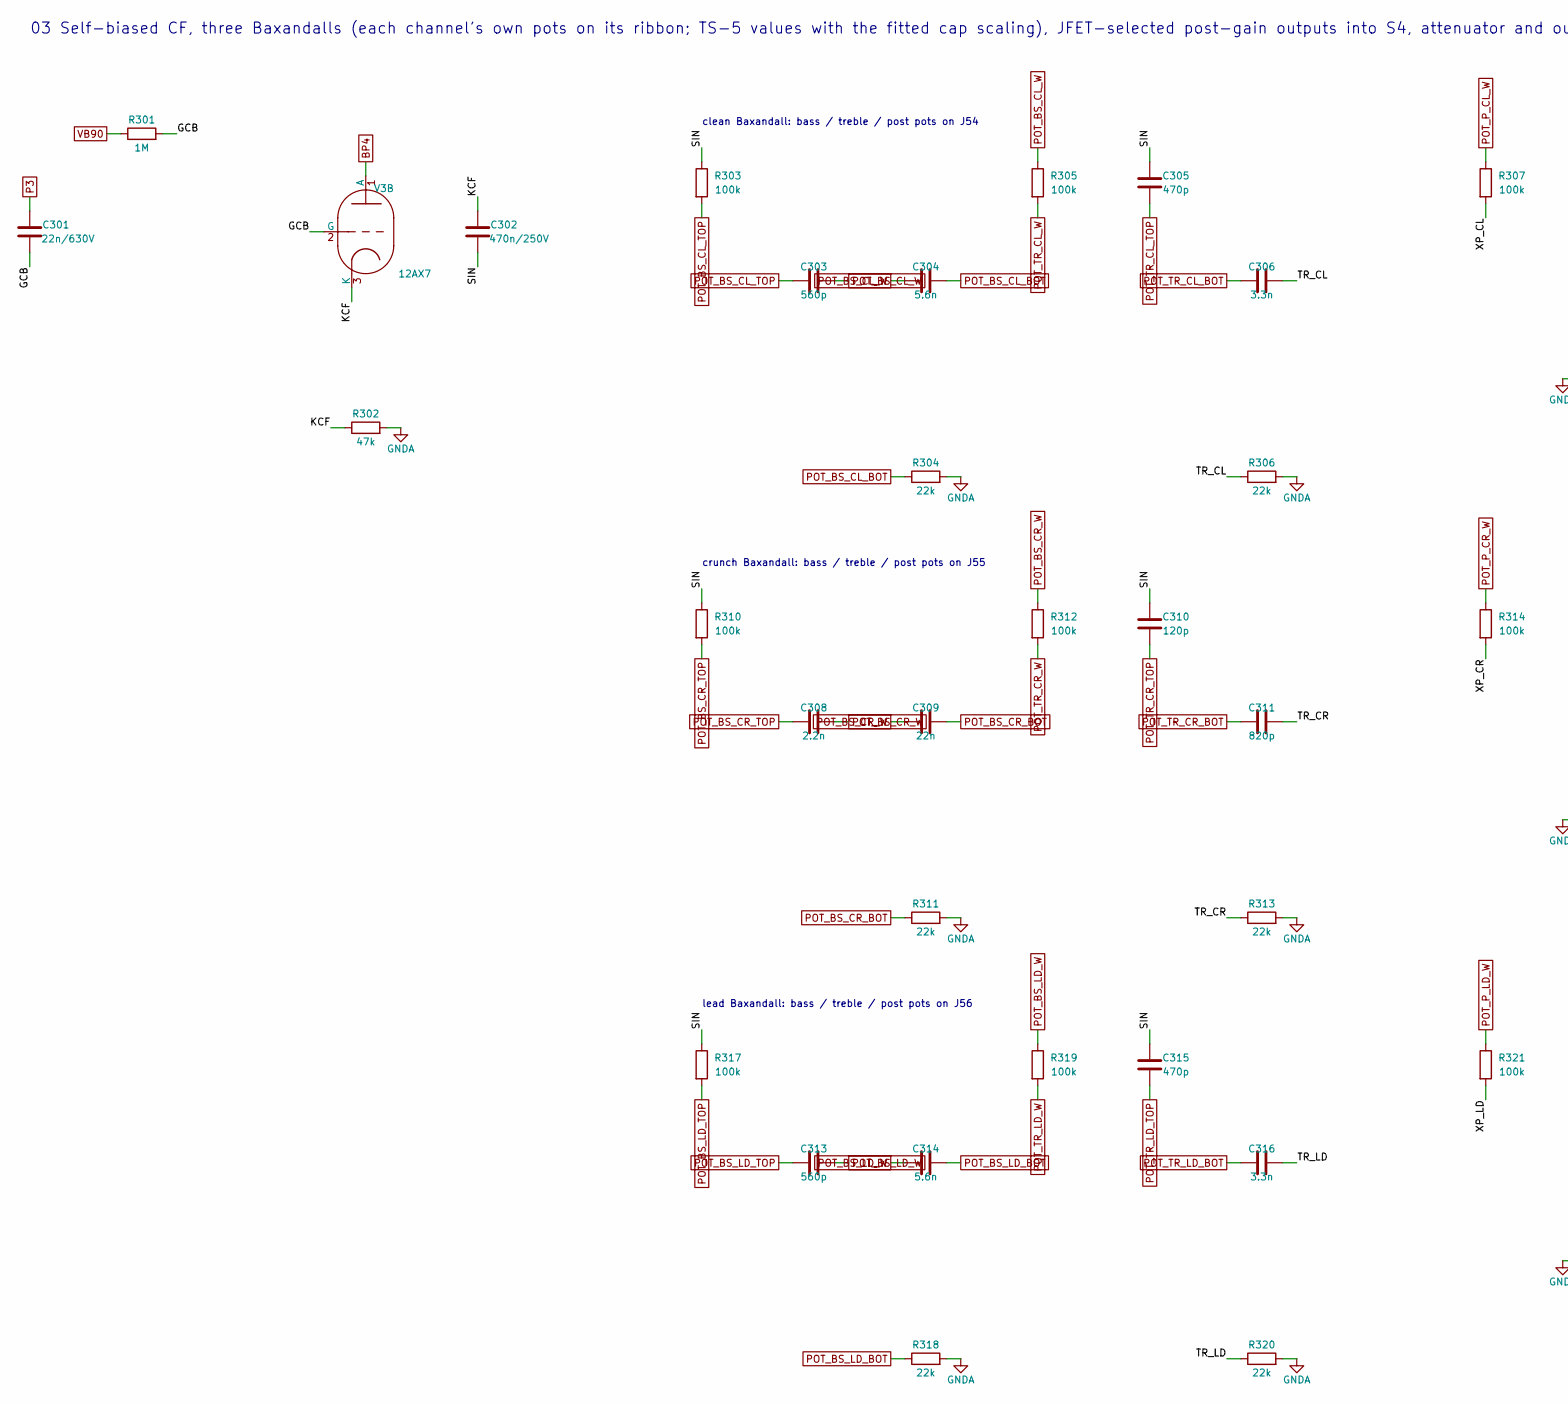
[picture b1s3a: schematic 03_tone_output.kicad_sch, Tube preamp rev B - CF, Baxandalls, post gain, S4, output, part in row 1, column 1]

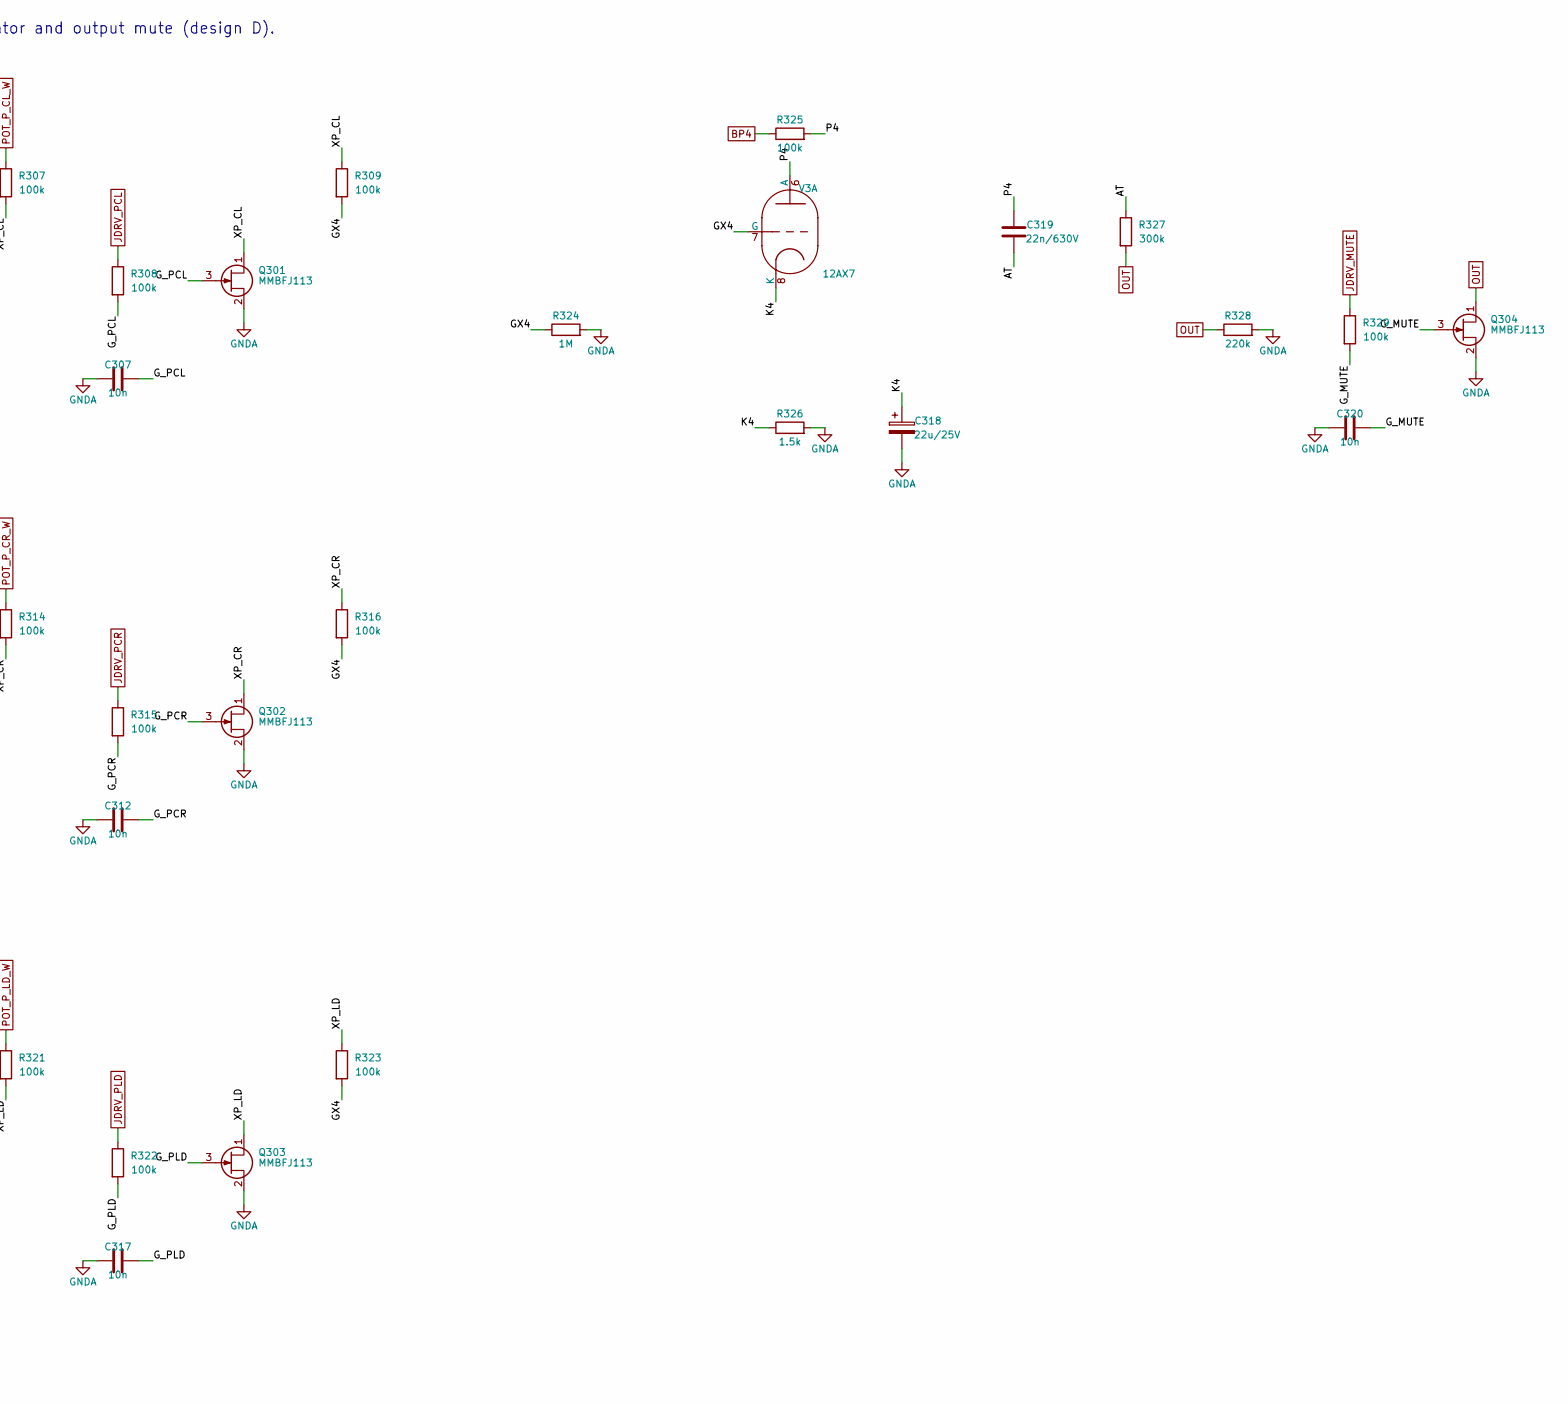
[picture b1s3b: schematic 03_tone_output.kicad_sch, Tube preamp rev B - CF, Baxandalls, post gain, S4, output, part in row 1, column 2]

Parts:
C301, C319: 22n/630V; C_Rect_L10.0mm_W4.0mm_P7.50mm_MKS4
C302: 470n/250V; C_Rect_L18.0mm_W8.0mm_P15.00mm_FKS3_FKP3
C303, C313: 560p; C_0805_2012Metric
C304, C314: 5.6n; C_0805_2012Metric
C305, C315: 470p; C_0805_2012Metric
C306, C316: 3.3n; C_0805_2012Metric
C307, C312, C317, C320: 10n; C_0603_1608Metric
C308: 2.2n; C_0805_2012Metric
C309: 22n; C_1206_3216Metric
C310: 120p; C_0805_2012Metric
C311: 820p; C_0805_2012Metric
C318: 22u/25V; CP_Elec_5x5.4
Q301, Q302, Q303, Q304: MMBFJ113; SOT-23
R301, R324: 1M; R_0805_2012Metric
R302: 47k; R_2512_6332Metric
R303, R305, R307, R309, R310, R312, R314, R316, R317, R319, R321, R323: 100k; R_0805_2012Metric
R304, R306, R311, R313, R318, R320: 22k; R_0805_2012Metric
R308, R315, R322, R329: 100k; R_0603_1608Metric
R325: 100k; R_2512_6332Metric
R326: 1.5k; R_0805_2012Metric
R327: 300k; R_0805_2012Metric
R328: 220k; R_0805_2012Metric
V3: 12AX7; Valve_Noval_Belton_PCD21.00mm

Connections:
/03 CF, Baxandalls, post gain, S4, output/AT: C319.2, R327.1
/03 CF, Baxandalls, post gain, S4, output/GCB: C301.2, R301.2, V3.2 (G)
/03 CF, Baxandalls, post gain, S4, output/GX4: R309.2, R316.2, R323.2, R324.1, V3.7 (G)
/03 CF, Baxandalls, post gain, S4, output/G_MUTE: C320.1, Q304.3 (G), R329.2
/03 CF, Baxandalls, post gain, S4, output/G_PCL: C307.1, Q301.3 (G), R308.2
/03 CF, Baxandalls, post gain, S4, output/G_PCR: C312.1, Q302.3 (G), R315.2
/03 CF, Baxandalls, post gain, S4, output/G_PLD: C317.1, Q303.3 (G), R322.2
/03 CF, Baxandalls, post gain, S4, output/K4: C318.1, R326.1, V3.8 (K)
/03 CF, Baxandalls, post gain, S4, output/KCF: C302.1, R302.1, V3.3 (K)
/03 CF, Baxandalls, post gain, S4, output/P4: C319.1, R325.2, V3.6 (A)
/03 CF, Baxandalls, post gain, S4, output/SIN: C302.2, C305.1, C310.1, C315.1, R303.1, R310.1, R317.1
/03 CF, Baxandalls, post gain, S4, output/TR_CL: C306.2, R306.1
/03 CF, Baxandalls, post gain, S4, output/TR_CR: C311.2, R313.1
/03 CF, Baxandalls, post gain, S4, output/TR_LD: C316.2, R320.1
/03 CF, Baxandalls, post gain, S4, output/XP_CL: Q301.1 (D), R307.2, R309.1
/03 CF, Baxandalls, post gain, S4, output/XP_CR: Q302.1 (D), R314.2, R316.1
/03 CF, Baxandalls, post gain, S4, output/XP_LD: Q303.1 (D), R321.2, R323.1
BP4: R325.1, V3.1 (A); also elsewhere on the board
GNDA: C307.2, C312.2, C317.2, C318.2, C320.2, Q301.2 (S), Q302.2 (S), Q303.2 (S), Q304.2 (S), R302.2, R304.2, R306.2, R311.2, R313.2, R318.2, R320.2, R324.2, R326.2, R328.2; also elsewhere on the board
JDRV_MUTE: R329.1; also elsewhere on the board
JDRV_PCL: R308.1; also elsewhere on the board
JDRV_PCR: R315.1; also elsewhere on the board
JDRV_PLD: R322.1; also elsewhere on the board
OUT: Q304.1 (D), R327.2, R328.1; also elsewhere on the board
P3: C301.1; also elsewhere on the board
POT_BS_CL_BOT: C304.2, R304.1; also elsewhere on the board
POT_BS_CL_TOP: C303.1, R303.2; also elsewhere on the board
POT_BS_CL_W: C303.2, C304.1, R305.1; also elsewhere on the board
POT_BS_CR_BOT: C309.2, R311.1; also elsewhere on the board
POT_BS_CR_TOP: C308.1, R310.2; also elsewhere on the board
POT_BS_CR_W: C308.2, C309.1, R312.1; also elsewhere on the board
POT_BS_LD_BOT: C314.2, R318.1; also elsewhere on the board
POT_BS_LD_TOP: C313.1, R317.2; also elsewhere on the board
POT_BS_LD_W: C313.2, C314.1, R319.1; also elsewhere on the board
POT_P_CL_W: R307.1; also elsewhere on the board
POT_P_CR_W: R314.1; also elsewhere on the board
POT_P_LD_W: R321.1; also elsewhere on the board
POT_TR_CL_BOT: C306.1; also elsewhere on the board
POT_TR_CL_TOP: C305.2; also elsewhere on the board
POT_TR_CL_W: R305.2; also elsewhere on the board
POT_TR_CR_BOT: C311.1; also elsewhere on the board
POT_TR_CR_TOP: C310.2; also elsewhere on the board
POT_TR_CR_W: R312.2; also elsewhere on the board
POT_TR_LD_BOT: C316.1; also elsewhere on the board
POT_TR_LD_TOP: C315.2; also elsewhere on the board
POT_TR_LD_W: R319.2; also elsewhere on the board
VB90: R301.1; also elsewhere on the board

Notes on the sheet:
03 Self-biased CF, three Baxandalls (each channel's own pots on its ribbon; TS-5 values with the fitted cap scaling), JFET-selected post-gain outputs into S4, attenuator and output mute (design D).
clean Baxandall: bass / treble / post pots on J54
crunch Baxandall: bass / treble / post pots on J55
lead Baxandall: bass / treble / post pots on J56
